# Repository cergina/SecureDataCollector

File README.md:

# SecureDataCollector (v 1.0)
###### Released on 09.05.2021; Works with SQL version 23

This is a repository of team-project 14 (SONET). Its aim is to preserve SW and HW related code.

##### Therefore I list my full HW relevant information, because it can be very important for you as well.
  - Glassfish 5.01
  - Java 8
  - MySQL 8.0.23
  - Nginx on school team server
  
To see what kind of dependencies this project has, see pom.xml file

### Some usefull links

| BRIEF DESCRIPTION | PATH |
| ------ | ------ |
| Official setup | [TIMAK.SETUP] |
| SQL init script | [TIMAK.SQL] |

### Help

| BRIEF DESCRIPTION | PATH |
| ------ | ------ |
| Team website | [TIMAK.WEB] |
| DCS System | [TIMAK.DCS] |

---

[//]: # (These are reference links used in the body of this note and get stripped out when the markdown processor does its job. There is no need to format nicely because it shouldn't be seen. Thanks SO - http://stackoverflow.com/questions/4823468/store-comments-in-markdown-syntax)

   [TIMAK.SETUP]: <https://drive.google.com/file/d/12LKXHPFGXoIBbkTN65K46eEUTF3nI9Sb/view?usp=sharing>
   [TIMAK.SQL]: <https://drive.google.com/file/d/1EdpjQeBai8ND4qpvn8RVNPXQaGzilRVe/view?usp=sharing>
   [TIMAK.WEB]: <https://team14-20.studenti.fiit.stuba.sk/>
   [TIMAK.DCS]: <https://team14-20.studenti.fiit.stuba.sk/dcs>

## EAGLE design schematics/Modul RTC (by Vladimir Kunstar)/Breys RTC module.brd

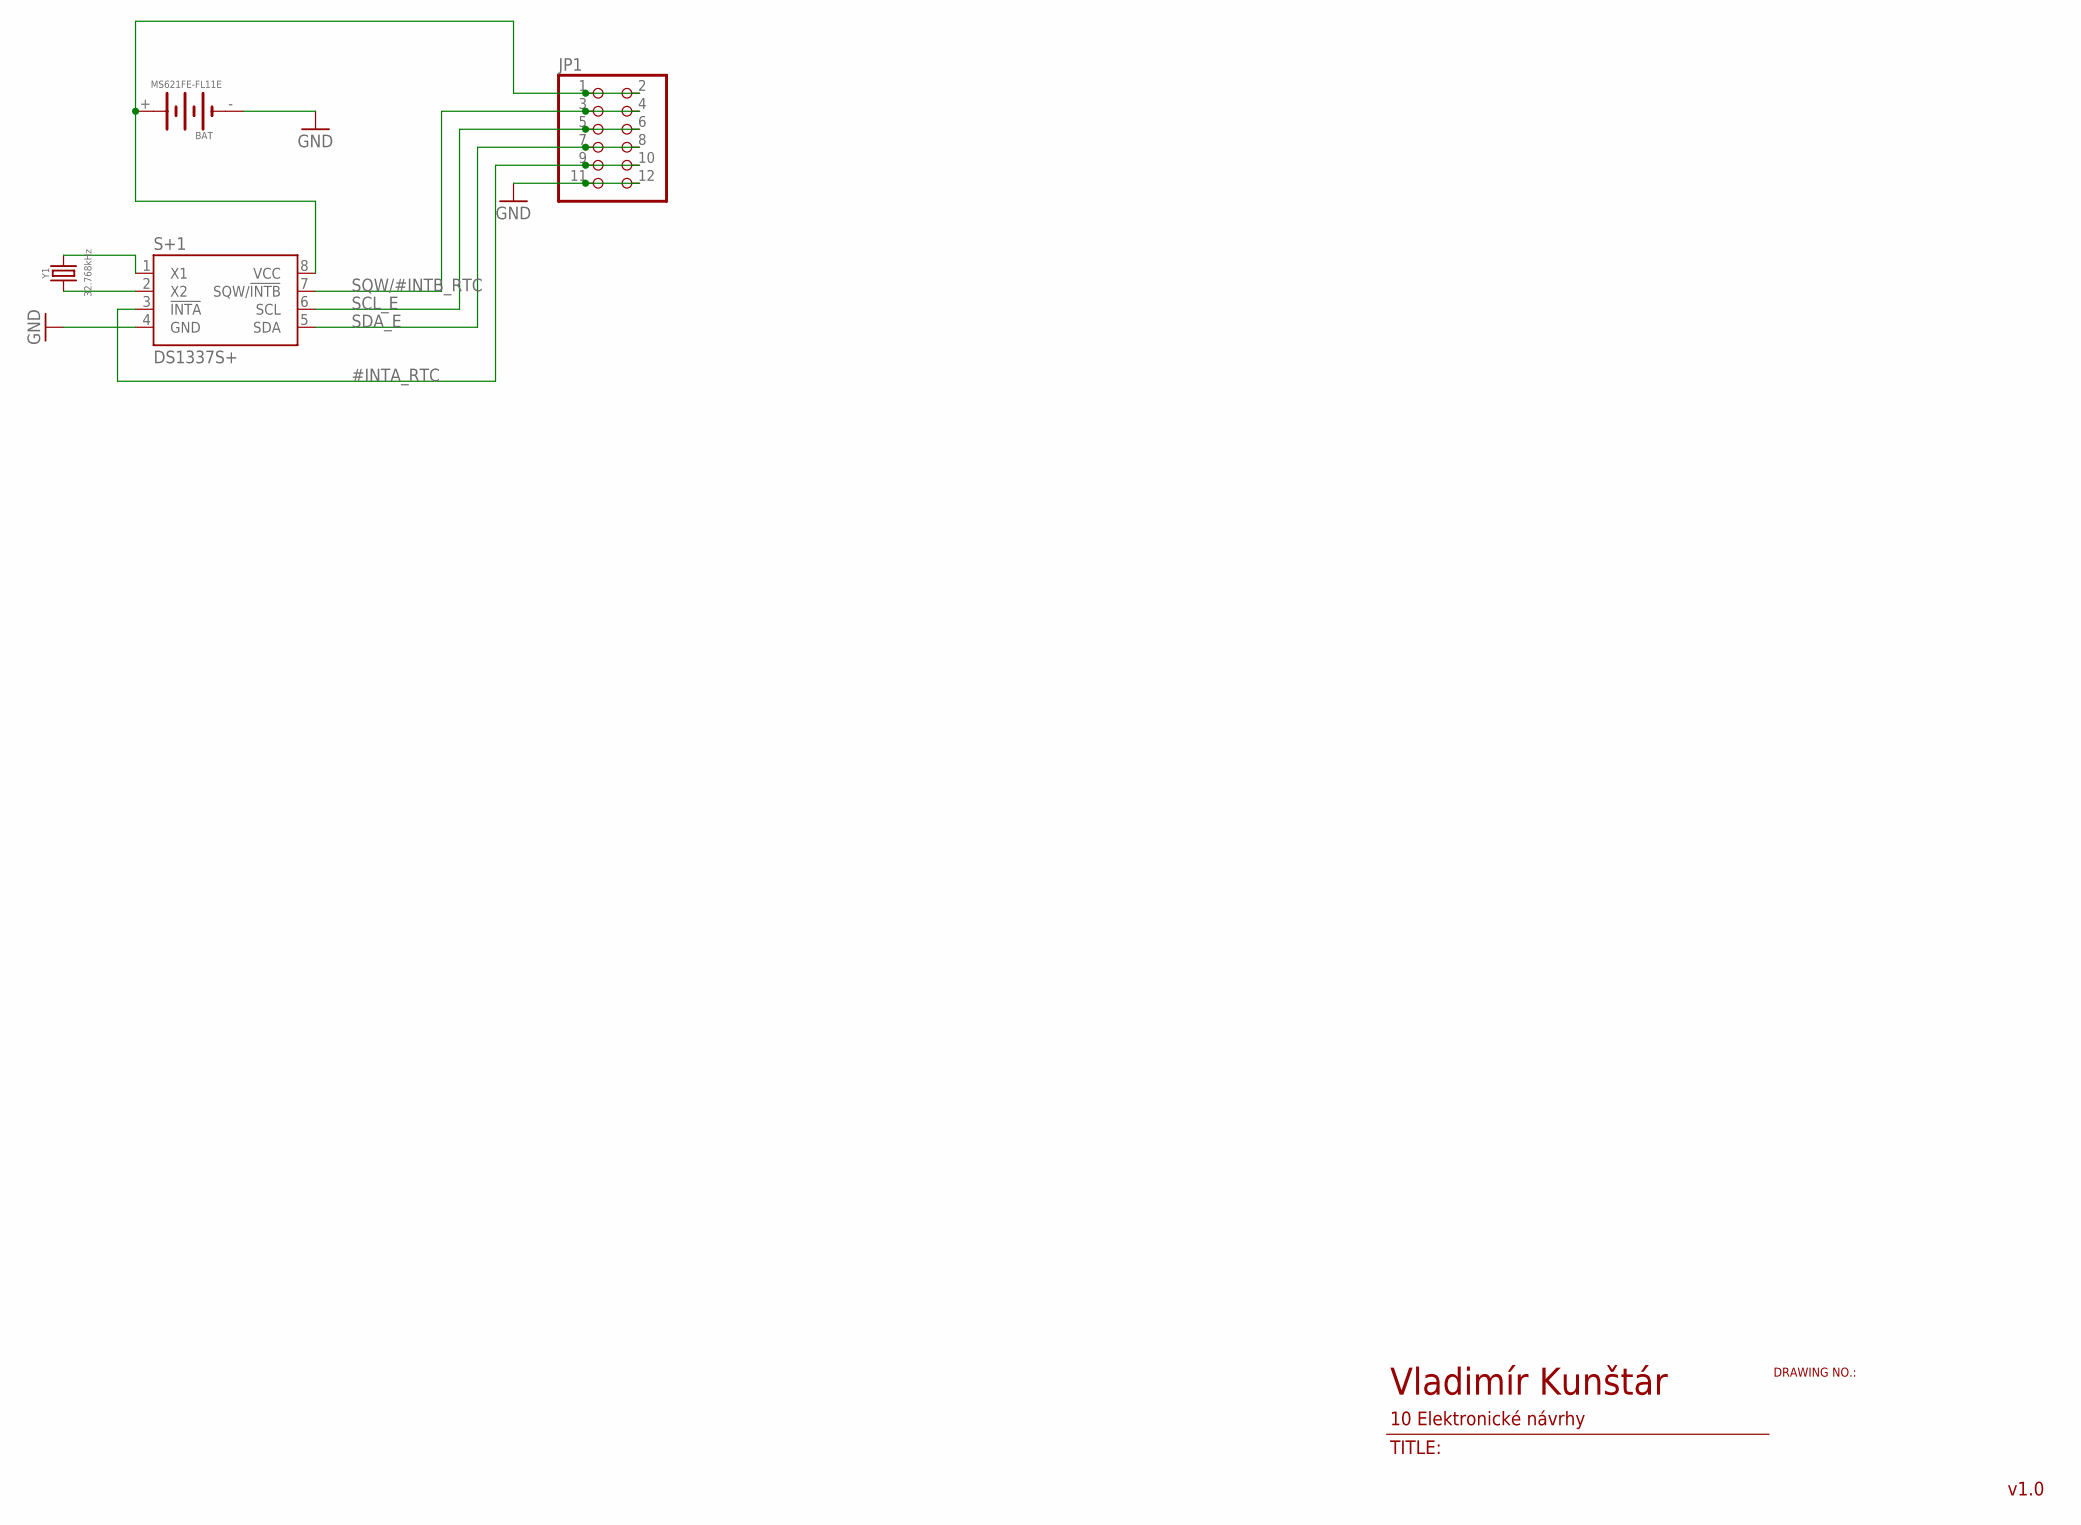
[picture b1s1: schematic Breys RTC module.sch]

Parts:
BAT: MS621FE-FL11E; MS621FEFL11E; FARNELL 1614634
JP1: PINHD-2X6; 2X06
S+1: DS1337S+; SO8
Y1: 32.768kHz; CFPX–217

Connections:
#INTA_RTC: JP1.9, JP1.10, S+1.3 (!INTA)
GND: BAT.-, JP1.11, JP1.12, S+1.4 (GND)
unnamed: BAT.+, JP1.1, JP1.2, S+1.8 (VCC)
unnamed: S+1.2 (X2), Y1.2
unnamed: S+1.1 (X1), Y1.1
SCL_E: JP1.5, JP1.6, S+1.6 (SCL)
SDA_E: JP1.7, JP1.8, S+1.5 (SDA)
SQW/#INTB_RTC: JP1.3, JP1.4, S+1.7 (SQW/!INTB!)

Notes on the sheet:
Vladimír Kunštár
10 Elektronické návrhy
DRAWING NO.:
TITLE:
v1.0

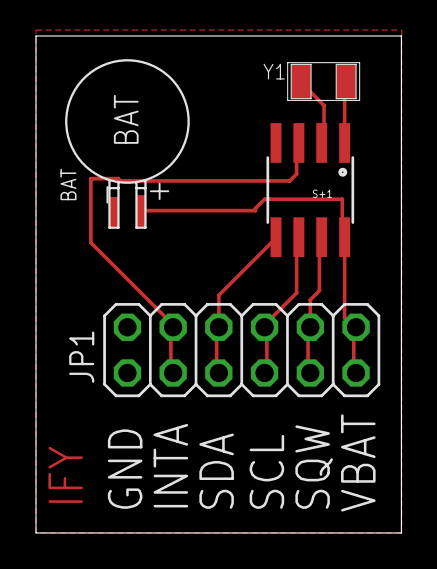
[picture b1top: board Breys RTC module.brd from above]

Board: 2 copper layers, 20.3 x 27.6 mm, 4 parts (0 on the bottom side), 8 nets.

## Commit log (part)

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2020-12-03 DataSource locally working
2020-12-16 E_CommType, E_SensorType, T_Address, T_CentralUnit should be working by now.
2020-12-16 POSTs for all implemented entities work
2020-12-20 Velké upratovanie + odstránená .idea
2020-12-20 FW: .gitignore
2020-12-20 FW: Pridaný LED blink testovací projekt (Atmega8)
2020-12-20 FW: Test uart na Atmega8
2020-12-22 POSTs and "GETs" via POST for all implemented entities work
2021-01-19 HTML "GUI" for showcase data from servers database works at /dcs/roadmap
2021-01-19 Logging + better GUI at Roadmap (on server some still does not work due to connection closed)
2021-01-20 Logging refactor
2021-02-24 Connection reestablishment possible fix
2021-02-24 Unnecessary code removal
2021-02-24 Refactor of code + more logs
2021-03-01 add bootstrap template
2021-03-01 clean-up
2021-03-02 Add template enggine
2021-03-03 Add .idea back
2021-03-08 Add inline styles, Resolve ambiguous constants
2021-03-09 minor fix for project rules
2021-03-11 Add static resources
2021-03-11 inherit servlet
2021-03-12 fragment templates
2021-03-12 Add register template, post request
2021-03-13 UTF-8, DB update, CSS and JS fix for server, favicon, other minor fixes
2021-03-13 login flow, sessions
2021-03-14 Merge remote-tracking branch 'origin/DCS-200' into DCS-216
    # Conflicts:
    # src/main/java/com/collector/web/IndexServlet.java
    # src/main/webapp/WEB-INF/templates/index.html
    # src/main/webapp/WEB-INF/web.xml
    /login and /register work
2021-03-15 create app layers, repackage, simplify base url detection
2021-03-15 remove sql from web layer
2021-03-15 Merge remote-tracking branch 'origin/DCS-200' into DCS-216
    # Conflicts:
    # src/main/java/com/collector/web/IndexServlet.java
    # src/main/webapp/WEB-INF/templates/index.html
    # src/main/webapp/WEB-INF/web.xml
    code refactor
2021-03-15 Pridávanie blokových schém + .gitignore
2021-03-15 Bloková schéma vstupov pre pripojenie meračov
2021-03-16 Merge remote-tracking branch 'origin/DCS-200' into DCS-216
    # Conflicts:
    # src/main/java/com/collector/web/IndexServlet.java
    # src/main/webapp/WEB-INF/templates/index.html
    # src/main/webapp/WEB-INF/web.xml
    fix non secure mysql syntax
2021-03-16 API correcting
2021-03-16 create app layers, repackage, remove sql from web layer
2021-03-16 small refactor
2021-03-16 Home screen improvement
2021-03-16 Implementation of MVC
2021-03-17 update gitignore
2021-03-17 Pridany CentralUnit Projekt
2021-03-18 user registration by admin, json processing
2021-03-21 ControllerUnit: funkcia pre tvorbu a poslanie packetu po uart-e
2021-03-21 Arduino sketch pre meranie na vstupoch (A7)
2021-03-21 CentralUnit: refaktor a upravy
2021-03-21 Implementation of user self registration, added hash table class, class for methods related to user access and exceptions for scenarios in self registration
2021-03-21 Minor fixes for the previous commit that contains self registration implementation
2021-03-22 Implementation of user registration by admin - generating, hashing and storing a verification code, getting the data about user from form and storing it, saving an entry to the access privilege journ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
2021-03-22 (not tested) include DCS-176
2021-03-23 (not tested) fix merge issues, add api response for use cases
2021-03-24 cover pessimistic scenaro for authentication, comment code
2021-03-24 fix minor issues, 1 db provider per context
2021-03-24 Rework for it to work on server
2021-03-24 CentralUnit: fix vypoctu crc, bridge medzi uart a uart1(debug purpose)
2021-03-25 CentrallUnit: quectel prototype
2021-03-26 fix db insert, pivilege logic, errors for GET requests
2021-03-26 Prototyp ovládača QUECTEL modemu.
2021-03-29 HTML and CSS files for authentication servlets
2021-03-29 part1
2021-03-29 part 2
2021-03-30 Important server improvements
2021-03-31 Review implementations
2021-03-31 rere
2021-03-31 display flat summary
2021-03-31 Home page background repaired and custom error sites
2021-04-01 [TEST ONLY] If after 24 hours login and other services will not fail, this commit will be permanent
2021-04-03 [TEST ONLY] If after 24 hours login and other services will not fail, this commit will be permanent v2
2021-04-04 [TEST ONLY] If after 24 hours login and other services will not fail, this commit will be permanent v4 : set autocommit to default always
2021-04-04 add create comm type servlet
2021-04-04 fix typo
2021-04-04 remove duplicate database model, add exists check
2021-04-04 fix uncomment
2021-04-04 Make creation of project possible + admin View reorganization
2021-04-04 Review implementation
2021-04-06 disposing connections, better css implementation, incorrect emails validation
2021-04-07 add create sensor type servlet
2021-04-07 Address addition - backend, kompletne pridavanie adries, osetrene duplikaty
2021-04-07 Password 2 times requirement and address, sensor type into admin panel addition
2021-04-08 DCS-260 Pridaný DIP address picker
2021-04-09 Specific flat view Improvement, addition of possibility to view it also by admin not only by specific user, Possibility to add controllerUnit for chosen flat
2021-04-09 ControllerUnit: zakald pre citanie analog pinu
2021-04-09 Minor Code Quality improvements
2021-04-09 Nices table view of controller units and sensors inside
2021-04-10 Fix bug that caused internal server error when no measurement for sensor was found
2021-04-10 varcharCheck makes sure exception is thrown
2021-04-11 ControllerUnit: citanie analog pinu ADC, implementovaný interupt pre PCINT
2021-04-11 Udrzba 6.2 cproj
2021-04-11 ControllerUnit: Pridané čítanie DIP address selektora
2021-04-11 CentralUnit: Pridané čítanie DIP address selektora + definície pinoutu pre ATmega128 a 2560
2021-04-12 index changes
2021-04-12 index changes 2
2021-04-12 controller unit servlet, create new sensor servlet
2021-04-13 change sensor input to dropdown
2021-04-13 ControllerUnit: pridaný základ pre sleep mode, refaktor
2021-04-13 Change password possible, salt unique for every new password for every user, request by outsider for controller by uid possible
2021-04-14 servlet: list types
2021-04-14 ControllerUnit: fixnuty sleep mode, pridany interupt na RX (PCINT16)
2021-04-14 Implementation of DCS-305 with newest
2021-04-15 Implementation of Shared UC
2021-04-15 Implementation of show all user's part
2021-04-16 Implementation of show precise centralUnit and addition of flat, flatowner and controllerUnit
2021-04-17 ControllerUnit: pridany interupt na TX, refaktor
2021-04-18 Implementation of review changes
2021-04-18 Graph added to flat view
2021-04-18 Minor corrections in code of graph implementation
2021-04-18 hotfix
2021-04-19 CentralUnit: refaktor, pridane uspavanie procesora
2021-04-19 Email sending basics
2021-04-19 Email sending after pre registration with verification code.... Code is ok. But somewhere on remote it does not work (not code fault)
2021-04-19 Refactor
2021-04-19 Remove unused imports
2021-04-19 CentralUnit: Odstránenie sleep funkcionality
2021-04-19 ControllerUnit: pridaný čas v správe pre central unit
2021-04-19 CentralUnit: fix kontroly crc
2021-04-19 fixing
2021-04-19 CentralUnit: Pridané knižnice eeprom_circular_buffer a jsmn (json)
2021-04-20 JSON for POST Measurements receive, preservation always (usable in case of failure, ...)
2021-04-20 CentralUnit: Fix vyradenia funkcionality quectelu z main loop
2021-04-20 Last supported version that will work with SQL version of 17
2021-04-20 JUnit5 tests of class Assurance - serve as example for other future tests
2021-04-20 Adding units to the graph and the scale is now changed dynamically
2021-04-20 Odstranenie console.log(), ktore boli pre testovacie ucely
2021-04-20 Revert "Delete GlassFish_5_0_1.xml"
    This reverts commit e368a9a5
2021-04-21 CentralUnit: Quectel 3G connectivity basics
2021-04-21 CentralUnit: Quectil fixes (working)
2021-04-21 after code review
2021-04-21 fix column class in html table
2021-04-21 ControllerUnit: pridany FS do protokolu
2021-04-21 CentrallUnit: spracovanie správy od kontroleru
2021-04-21 Awaiting fix for graph show in flat view
2021-04-21 Fix of steps on the Y-scale
2021-04-21 CentralUnit: Quectel measurement send
2021-04-22 Better validation for UID/ID requests
2021-04-22 list projects
2021-04-22 Addition of project view to specific user view
2021-04-23 specific project
2021-04-24 list all users for project
2021-04-24 Little bit of view change
2021-04-24 Retrieve [by id] from database is made into generics
2021-04-24 FIX for bad merge
2021-04-25 Schematic: TTL logic level converter
2021-04-25 TTL logic level converter pridaný TX_3V3 label
2021-04-25 TTL logic level converter prehodenie 5V a 3V3
2021-04-26 x/action/buildings?id=
2021-04-26 small fix for req view input
2021-04-26 ControllerUnit: Removed attempts to free static variables
2021-04-26 ControllerUnit: EEPROM funkcionalita (buffer1 init)
2021-04-27 Building addition (choice from unused addresses) inside project
2021-04-27 Building addition (choice from unused addresses) inside project, Review implementation
2021-04-27 Unify coding style
2021-04-27 resolve confilcts
2021-04-27 resolve conflicts
2021-04-27 Flat addition inside building
2021-04-28 Review for flat addition + fix for reload required to succesfully add new flat in the same window
2021-04-28 add notification when attempting to add controller to flat that does not have a central unit yet
2021-05-01 reuse tables in flat summary, display flat owners
2021-05-01 finalize single central unit view
2021-05-01 Adding a graph to the consumption page
2021-05-02 add new central unit
2021-05-02 Added graph to consumption view
2021-05-02 Added graph to building view
2021-05-02 CSS fix + useless work (to be kept for future db improvements)
2021-05-02 fix with overview building
2021-05-02 Schematic: RTC Test module provided by product owner
2021-05-03 Controller: Integrovaná RTC knižnica
2021-05-03 Fixed interaction with database for flats and changed text in registration
2021-05-03 Readme for release
2021-05-03 Options that secure that running on ubuntu server works straight out of package
2021-05-03 schema version 20
2021-05-04 CentralUnit: String tools
2021-05-04 CentralUnit: Current proto identification over UART
2021-05-04 CentralUnit: Measurement JSON composition functionality
2021-05-04 CentralUnit: Measurement POST functionality
2021-05-04 CentralUnit: method for msg parse, added struct Measurement
2021-05-05 Uprava HTML a CSS, treba este opravit tabulky, kedze pretekaju
2021-05-05 CentralUnit: measurement POST fix
2021-05-05 CentralUnit: uprave PacketParse
2021-05-05 html table example
2021-05-05 proper html tables
2021-05-07 Small design improvements
2021-05-07 Mobile view addition to home screen
2021-05-07 DCS-402, DCS-398, DCS-401
2021-05-07 DCS-385,DCS-403 : user information of reasons of inserts failure
2021-05-08 Addition of problem view functionality
2021-05-08 Implementation of review remark
2021-05-08 Added a servlet for viewing user creations, tasks: DCS-397 + DCS-396 + DCS-395 combined
2021-05-09 Implemented remarks from the code review - deleted the .xml file, added a link to index page, changed the name of the scenario
2021-05-09 Final fix of User Creation logs view
2021-05-09 ControlerUnit: Zwave measure transfer
2021-05-09 Fix of leaked connections in graphs and optimalization of code in graphs
2021-05-09 Finishing touch
2021-05-09 CentralUnit: Disable debug output over UART
2021-05-09 Schematic: Optocoupler element for Z-Wave interaction on controller.
2021-05-10 Security updates
2021-05-10 Security updates review
2021-05-10 Production ready
2021-05-10 HTML refinement, Mail works
2021-05-12 header design log out link html fix
2021-05-12 to work on server straightaway
2021-05-21 Final schemtaic: Central unit

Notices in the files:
parts and their libraries:
AjRTC: This is v1 and is licensed under the Creative Commons (Attribution-Non-Commercial-Share Alike 2.0 UK)
